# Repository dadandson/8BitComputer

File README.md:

# 8BitComputer
Hold eagle design for pcbs based on Ben Eaters 8 bit computer via bread boards

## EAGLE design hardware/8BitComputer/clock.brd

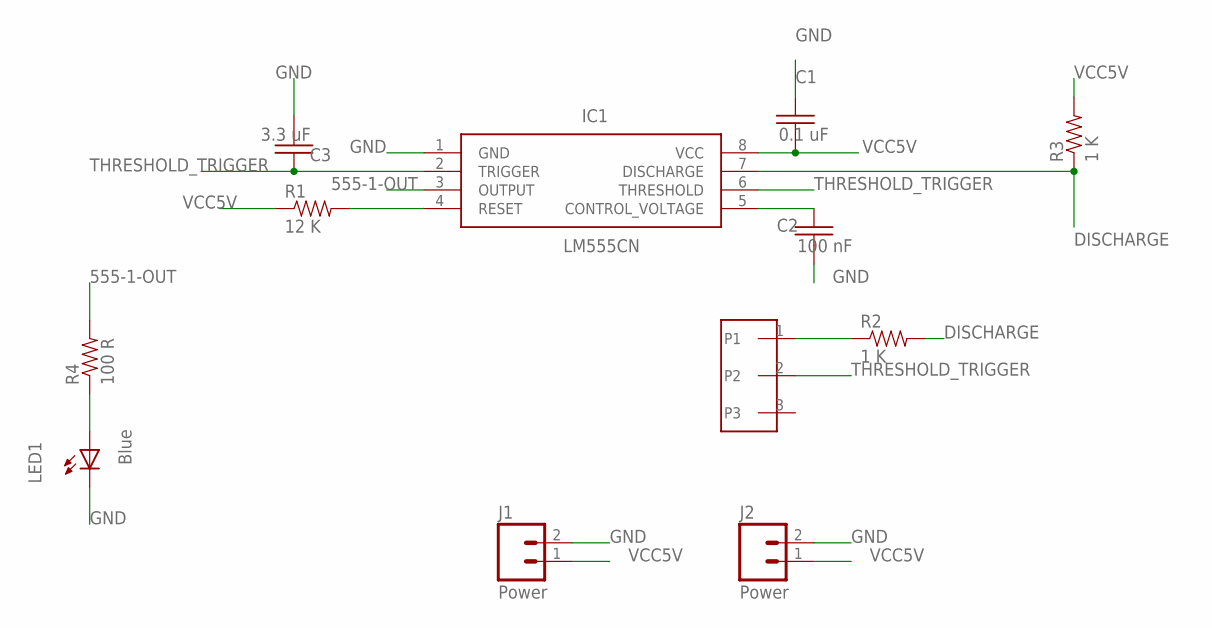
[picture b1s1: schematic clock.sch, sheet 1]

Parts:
C1: 0.1 uF; C0805
C2: 100 nF; C0805K
C3: 3.3 uF; C0805
IC1: LM555CN; DIP762W53P254L980H533Q8N
J1, J2: Power; 1X02
LED1: Blue; LED3MM-NS
R1: 12 K; 0805
R2, R3: 1 K; 0805
R4: 100 R; 0805
U$1: SQUARE-TRIMPOT-POTENTIOMETER; 3/8-SQUARE-TRIMPOT

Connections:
555-1-OUT: IC1.3 (OUTPUT), R4.2; also elsewhere on the board
DISCHARGE: IC1.7 (DISCHARGE), R2.2, R3.1
GND: C1.1, C2.2, C3.2, IC1.1 (GND), J1.2, J2.2, LED1.K (C); also elsewhere on the board
unnamed: IC1.4 (RESET), R1.2
unnamed: C2.1, IC1.5 (CONTROL_VOLTAGE)
unnamed: R2.1, U$1.1
unnamed: LED1.A, R4.1
THRESHOLD_TRIGGER: C3.1, IC1.2 (TRIGGER), IC1.6 (THRESHOLD), U$1.2
VCC5V: C1.2, IC1.8 (VCC), J1.1, J2.1, R1.1, R3.2; also elsewhere on the board

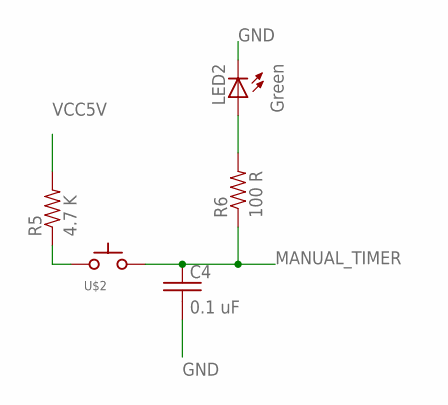
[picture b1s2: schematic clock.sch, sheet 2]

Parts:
C4: 0.1 uF; C0805
LED2: Green; LED3MM-NS
R5: 4.7 K; 0805
R6: 100 R; 0805
U$2: SWITCH_TACTILETACTILE_PIN; TACTILE-PTH

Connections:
GND: C4.2, LED2.K (C); also elsewhere on the board
MANUAL_TIMER: C4.1, R6.1, U$2.1 (A), U$2.2 (A); also elsewhere on the board
unnamed: LED2.A, R6.2
unnamed: R5.1, U$2.3 (C), U$2.4 (C)
VCC5V: R5.2; also elsewhere on the board

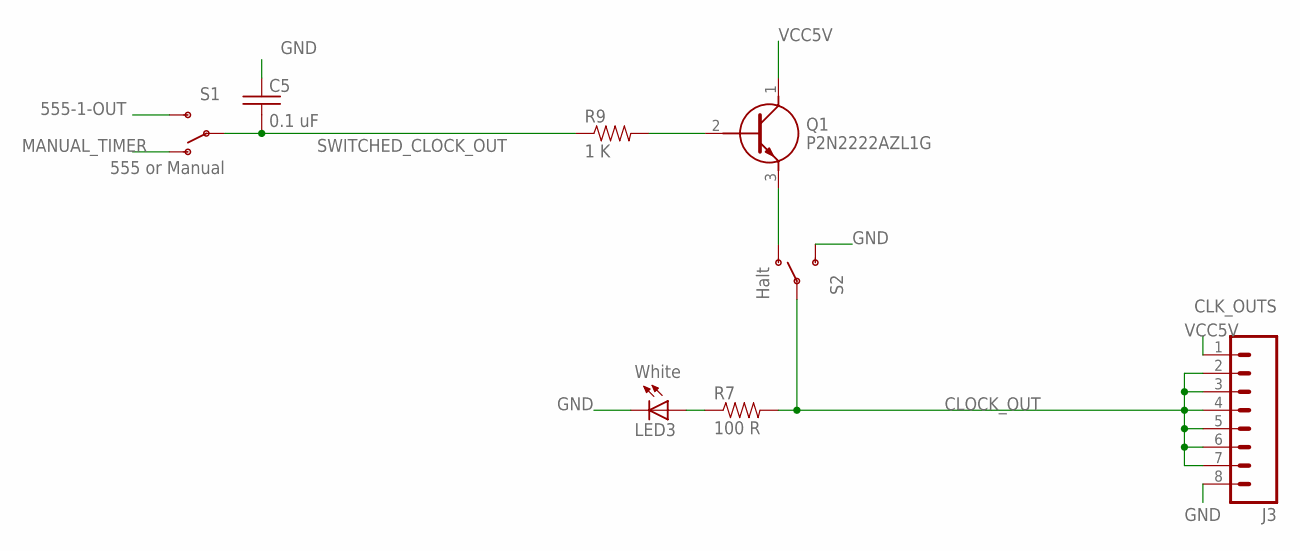
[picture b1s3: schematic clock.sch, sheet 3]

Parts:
C5: 0.1 uF; C0805
J3: CLK_OUTS; 1X08
LED3: White; LED3MM-NS
Q1: P2N2222AZL1G; 2N6027
R7: 100 R; 0805
R9: 1 K; 0805
S1: 555 or Manual; SWITCH-SPDT_KIT
S2: Halt; SWITCH-SPDT_KIT

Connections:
555-1-OUT: S1.3 (S); also elsewhere on the board
CLOCK_OUT: J3.2, J3.3, J3.4, J3.5, J3.6, J3.7, R7.2, S2.2
GND: C5.1, J3.8, LED3.K (C), S2.3 (S); also elsewhere on the board
MANUAL_TIMER: S1.1 (O); also elsewhere on the board
unnamed: LED3.A, R7.1
unnamed: Q1.3 (E), S2.1 (O)
unnamed: Q1.2 (B), R9.2
SWITCHED_CLOCK_OUT: C5.2, R9.1, S1.2
VCC5V: J3.1, Q1.1 (C); also elsewhere on the board

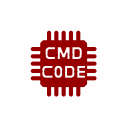
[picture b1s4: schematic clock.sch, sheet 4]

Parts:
U$3: CMD_C0DE_LOGOCMD_CODE_LOGO_TOP_COPPER; CMD_C0DE_LOGO_TOP_COPPER

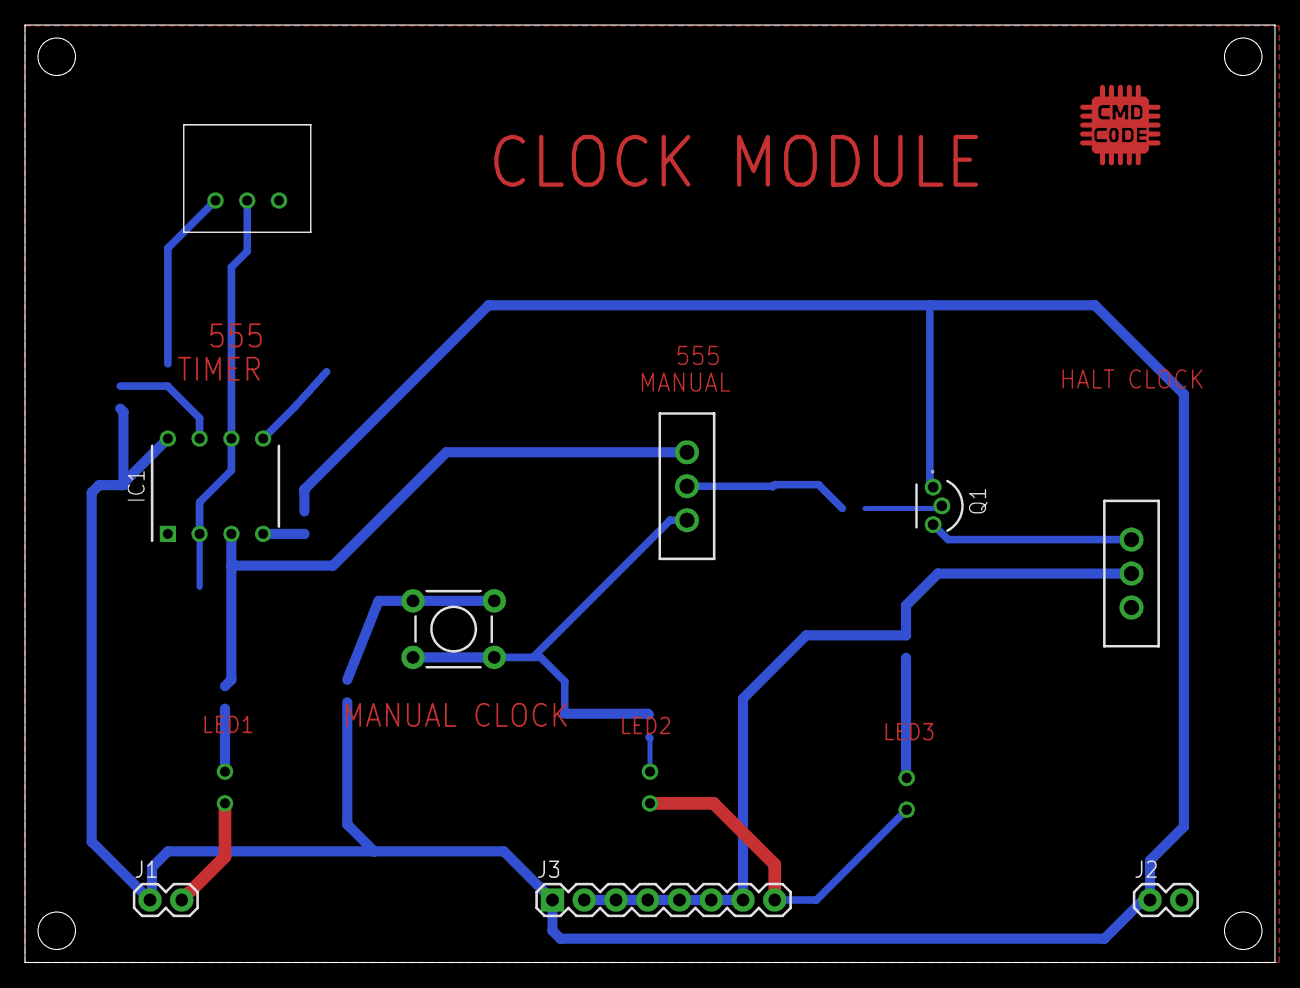
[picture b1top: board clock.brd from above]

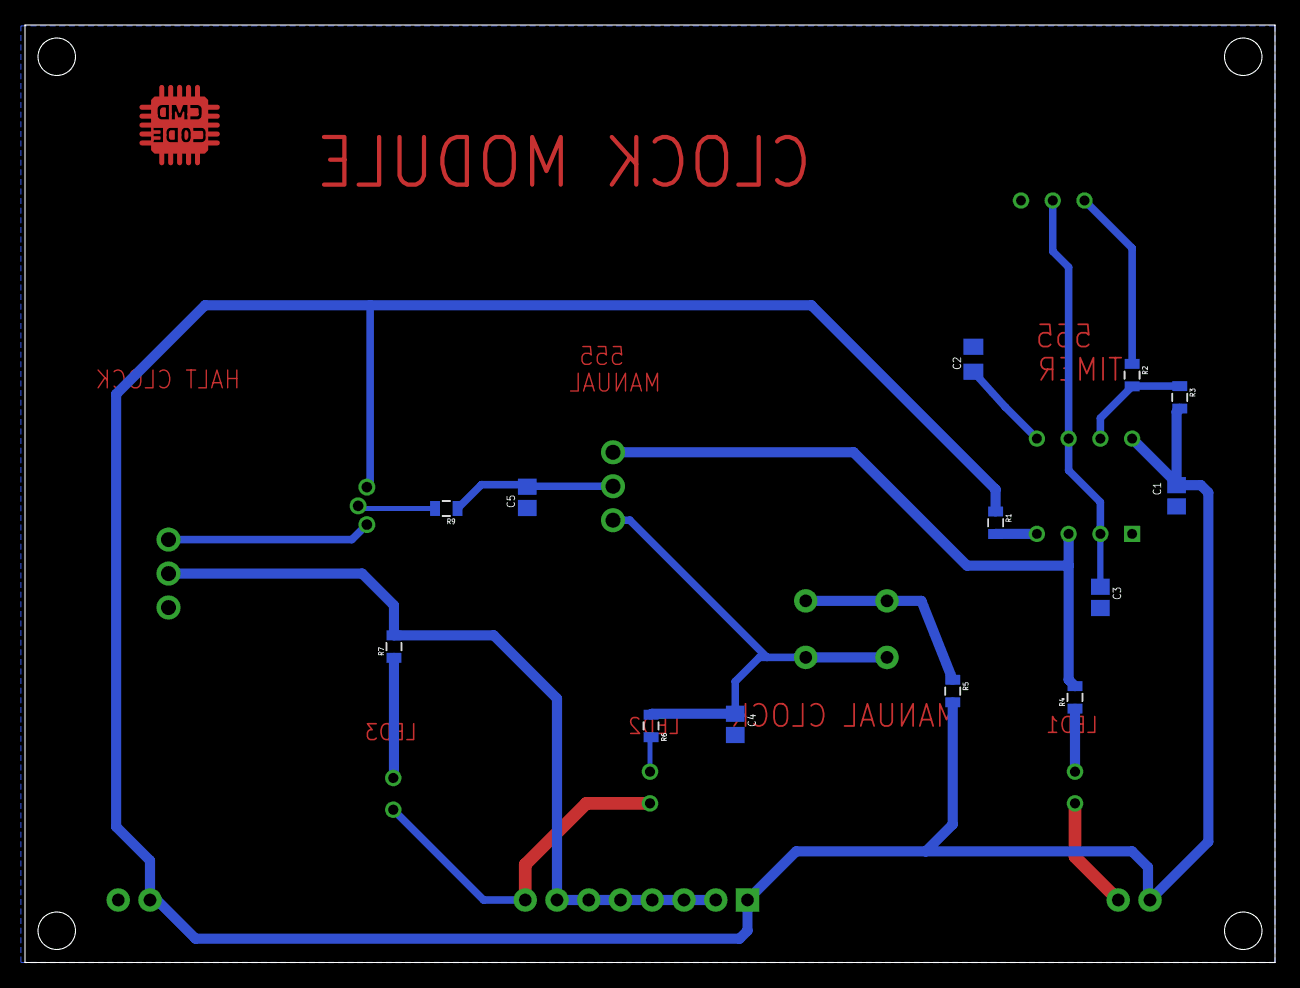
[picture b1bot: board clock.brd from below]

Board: 2 copper layers, 100.0 x 75.0 mm, 26 parts (13 on the bottom side), 17 nets.

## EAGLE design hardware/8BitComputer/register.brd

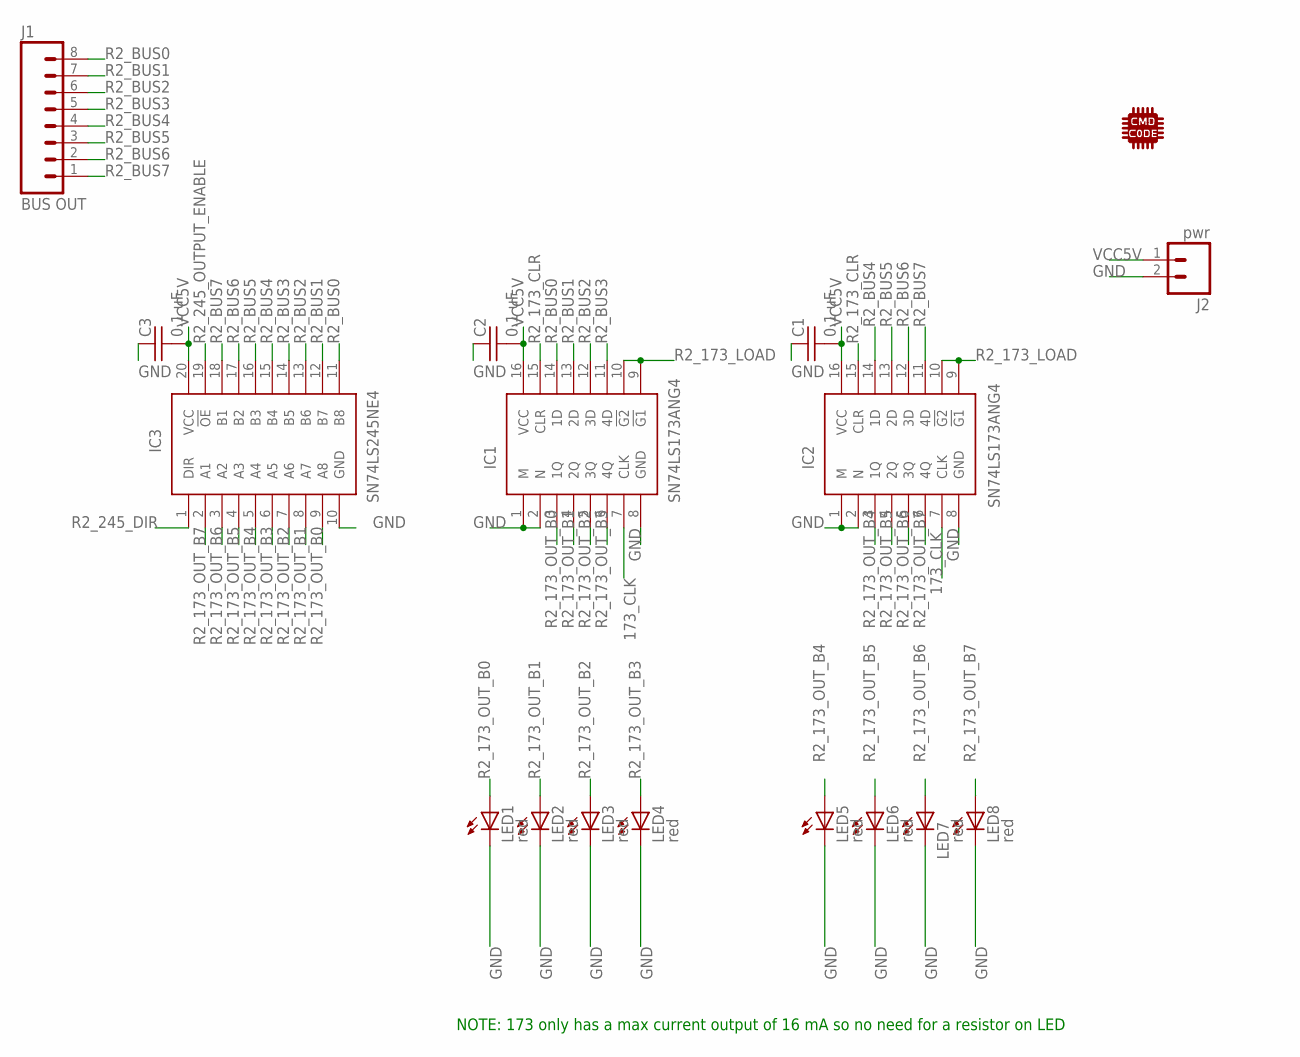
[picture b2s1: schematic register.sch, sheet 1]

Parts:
C1, C2, C3: 0.1 uF; C075-032X103
IC1, IC2: SN74LS173ANG4; DIP794W53P254L1930H508Q16N
IC3: SN74LS245NE4; DIP794W53P254L2540H508Q20N
J1: BUS OUT; 1X08_ROUND
J2: pwr; 1X02
LED1, LED2, LED3, LED4, LED5, LED6, LED7, LED8: red; LED3MM
U$1: CMD_C0DE_LOGOCMD_CODE_LOGO_TOP_COPPER; CMD_C0DE_LOGO_TOP_COPPER

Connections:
173_CLK: IC1.7 (CLK), IC2.7 (CLK); also elsewhere on the board
GND: C1.1, C2.1, C3.1, IC1.1 (M), IC1.2 (N), IC1.8 (GND), IC2.1 (M), IC2.2 (N), IC2.8 (GND), IC3.10 (GND), J2.2, LED1.K (C), LED2.K (C), LED3.K (C), LED4.K (C), LED5.K (C), LED6.K (C), LED7.K (C), LED8.K (C); also elsewhere on the board
R2_173_CLR: IC1.15 (CLR), IC2.15 (CLR); also elsewhere on the board
R2_173_LOAD: IC1.9 (!G1), IC1.10 (!G2), IC2.9 (!G1), IC2.10 (!G2); also elsewhere on the board
R2_173_OUT_B0: IC1.3 (1Q), IC3.9 (A8), LED1.A
R2_173_OUT_B1: IC1.4 (2Q), IC3.8 (A7), LED2.A
R2_173_OUT_B2: IC1.5 (3Q), IC3.7 (A6), LED3.A
R2_173_OUT_B3: IC1.6 (4Q), IC3.6 (A5), LED4.A
R2_173_OUT_B4: IC2.3 (1Q), IC3.5 (A4), LED5.A
R2_173_OUT_B5: IC2.4 (2Q), IC3.4 (A3), LED6.A
R2_173_OUT_B6: IC2.5 (3Q), IC3.3 (A2), LED7.A
R2_173_OUT_B7: IC2.6 (4Q), IC3.2 (A1), LED8.A
R2_245_DIR: IC3.1 (DIR); also elsewhere on the board
R2_245_OUTPUT_ENABLE: IC3.19 (!OE); also elsewhere on the board
R2_BUS0: IC1.14 (1D), IC3.11 (B8), J1.8
R2_BUS1: IC1.13 (2D), IC3.12 (B7), J1.7
R2_BUS2: IC1.12 (3D), IC3.13 (B6), J1.6
R2_BUS3: IC1.11 (4D), IC3.14 (B5), J1.5
R2_BUS4: IC2.14 (1D), IC3.15 (B4), J1.4
R2_BUS5: IC2.13 (2D), IC3.16 (B3), J1.3
R2_BUS6: IC2.12 (3D), IC3.17 (B2), J1.2
R2_BUS7: IC2.11 (4D), IC3.18 (B1), J1.1
VCC5V: C1.2, C2.2, C3.2, IC1.16 (VCC), IC2.16 (VCC), IC3.20 (VCC), J2.1; also elsewhere on the board

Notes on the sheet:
NOTE: 173 only has a max current output of 16 mA so no need for a resistor on LED

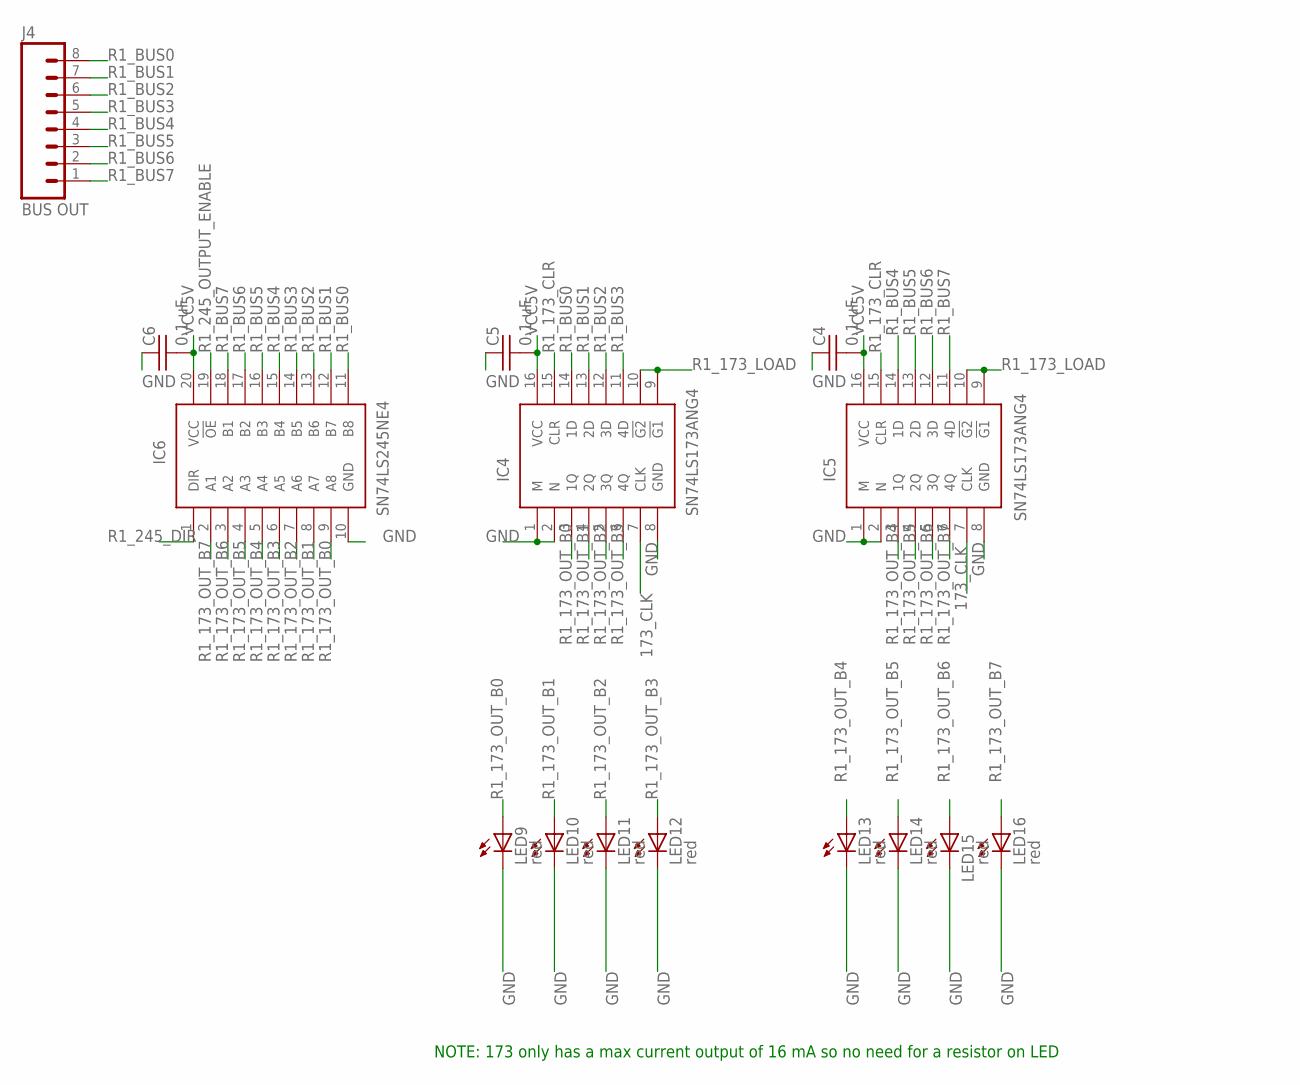
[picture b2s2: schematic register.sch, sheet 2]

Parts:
C4, C5, C6: 0.1 uF; C075-032X103
IC4, IC5: SN74LS173ANG4; DIP794W53P254L1930H508Q16N
IC6: SN74LS245NE4; DIP794W53P254L2540H508Q20N
J4: BUS OUT; 1X08_ROUND
LED9, LED10, LED11, LED12, LED13, LED14, LED15, LED16: red; LED3MM

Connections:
173_CLK: IC4.7 (CLK), IC5.7 (CLK); also elsewhere on the board
GND: C4.1, C5.1, C6.1, IC4.1 (M), IC4.2 (N), IC4.8 (GND), IC5.1 (M), IC5.2 (N), IC5.8 (GND), IC6.10 (GND), LED9.K (C), LED10.K (C), LED11.K (C), LED12.K (C), LED13.K (C), LED14.K (C), LED15.K (C), LED16.K (C); also elsewhere on the board
R1_173_CLR: IC4.15 (CLR), IC5.15 (CLR); also elsewhere on the board
R1_173_LOAD: IC4.9 (!G1), IC4.10 (!G2), IC5.9 (!G1), IC5.10 (!G2); also elsewhere on the board
R1_173_OUT_B0: IC4.3 (1Q), IC6.9 (A8), LED9.A
R1_173_OUT_B1: IC4.4 (2Q), IC6.8 (A7), LED10.A
R1_173_OUT_B2: IC4.5 (3Q), IC6.7 (A6), LED11.A
R1_173_OUT_B3: IC4.6 (4Q), IC6.6 (A5), LED12.A
R1_173_OUT_B4: IC5.3 (1Q), IC6.5 (A4), LED13.A
R1_173_OUT_B5: IC5.4 (2Q), IC6.4 (A3), LED14.A
R1_173_OUT_B6: IC5.5 (3Q), IC6.3 (A2), LED15.A
R1_173_OUT_B7: IC5.6 (4Q), IC6.2 (A1), LED16.A
R1_245_DIR: IC6.1 (DIR); also elsewhere on the board
R1_245_OUTPUT_ENABLE: IC6.19 (!OE); also elsewhere on the board
R1_BUS0: IC4.14 (1D), IC6.11 (B8), J4.8
R1_BUS1: IC4.13 (2D), IC6.12 (B7), J4.7
R1_BUS2: IC4.12 (3D), IC6.13 (B6), J4.6
R1_BUS3: IC4.11 (4D), IC6.14 (B5), J4.5
R1_BUS4: IC5.14 (1D), IC6.15 (B4), J4.4
R1_BUS5: IC5.13 (2D), IC6.16 (B3), J4.3
R1_BUS6: IC5.12 (3D), IC6.17 (B2), J4.2
R1_BUS7: IC5.11 (4D), IC6.18 (B1), J4.1
VCC5V: C4.2, C5.2, C6.2, IC4.16 (VCC), IC5.16 (VCC), IC6.20 (VCC); also elsewhere on the board

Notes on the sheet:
NOTE: 173 only has a max current output of 16 mA so no need for a resistor on LED

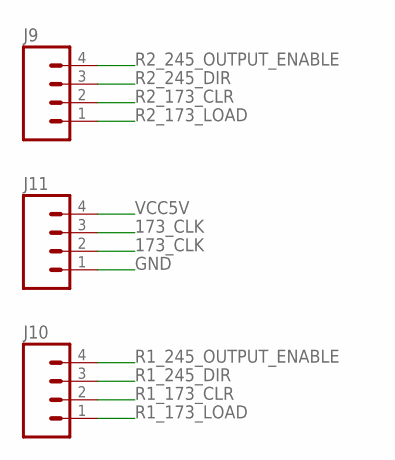
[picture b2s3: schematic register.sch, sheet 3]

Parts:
J9, J10, J11: M04PTH; 1X04

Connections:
173_CLK: J11.2, J11.3; also elsewhere on the board
GND: J11.1; also elsewhere on the board
R1_173_CLR: J10.2; also elsewhere on the board
R1_173_LOAD: J10.1; also elsewhere on the board
R1_245_DIR: J10.3; also elsewhere on the board
R1_245_OUTPUT_ENABLE: J10.4; also elsewhere on the board
R2_173_CLR: J9.2; also elsewhere on the board
R2_173_LOAD: J9.1; also elsewhere on the board
R2_245_DIR: J9.3; also elsewhere on the board
R2_245_OUTPUT_ENABLE: J9.4; also elsewhere on the board
VCC5V: J11.4; also elsewhere on the board

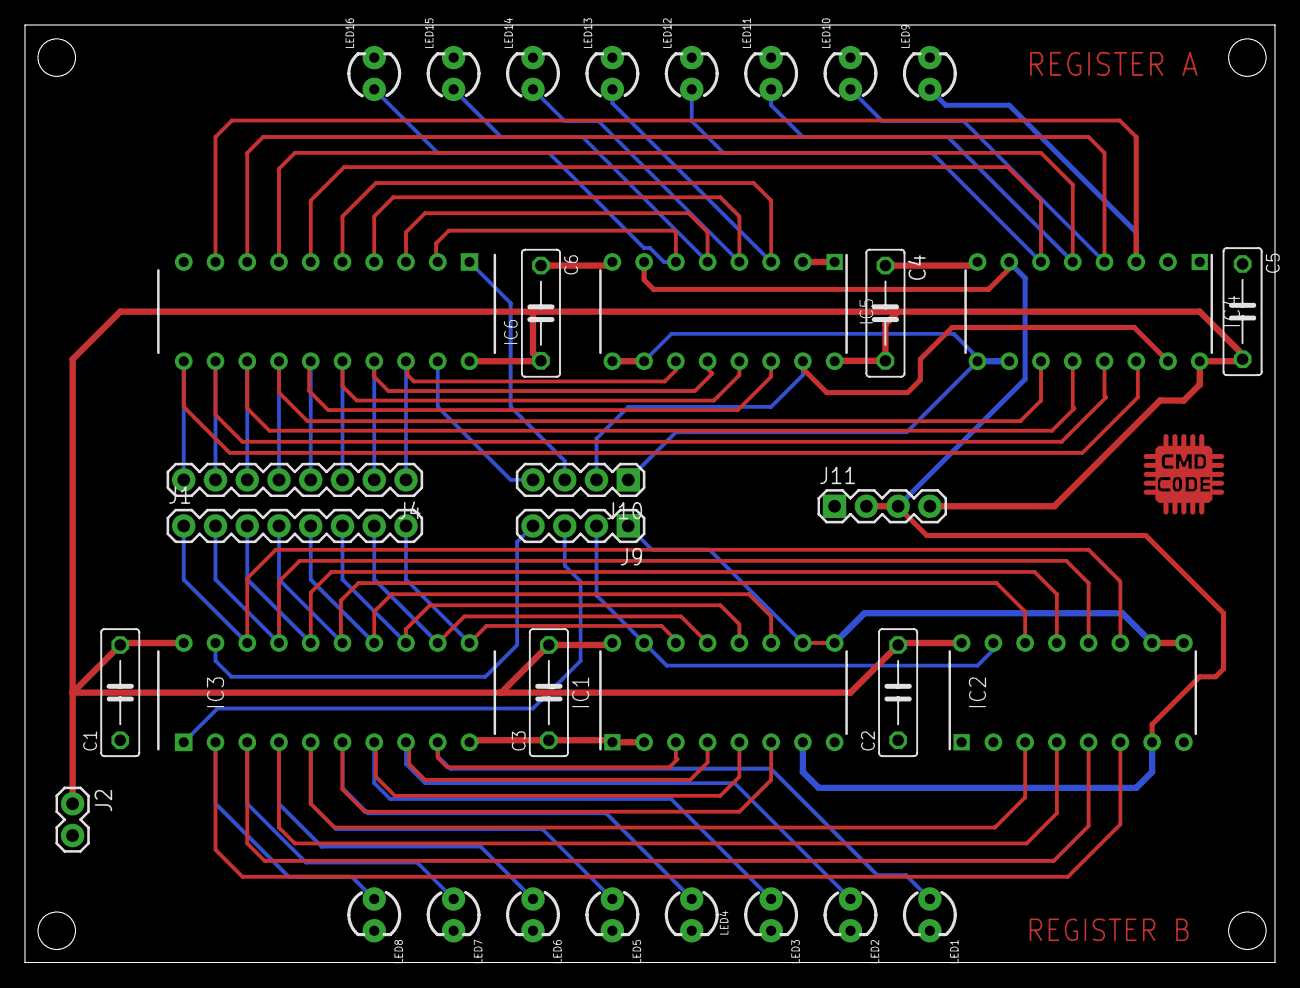
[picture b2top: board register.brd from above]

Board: 2 copper layers, 100.0 x 75.0 mm, 35 parts (0 on the bottom side), 43 nets.

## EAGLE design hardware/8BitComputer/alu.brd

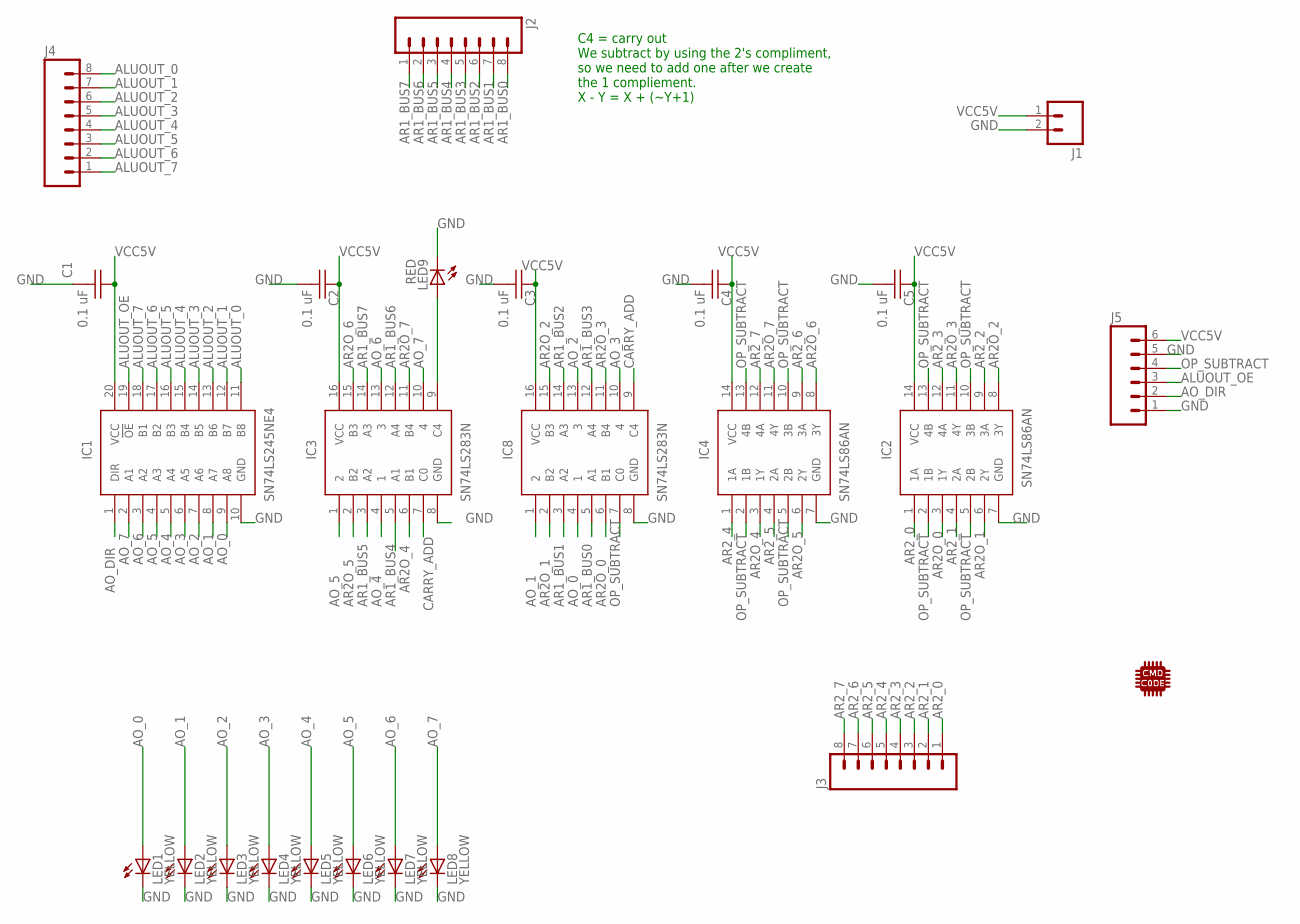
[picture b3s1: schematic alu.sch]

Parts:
C1, C2, C3, C4, C5: 0.1 uF; C050-025X075
IC1: SN74LS245NE4; DIP794W53P254L2540H508Q20N
IC2, IC4: SN74LS86AN; DIP254P762X508-14
IC3, IC8: SN74LS283N; DIP254P762X508-16
J1: M02PTH; 1X02
J2, J3, J4: M08SILK_FEMALE_PTH; 1X08
J5: M06SILK_FEMALE_PTH; 1X06
LED1, LED2, LED3, LED4, LED5, LED6, LED7, LED8: YELLOW; LED3MM-NS
LED9: RED; LED3MM-NS
U$1: CMD_C0DE_LOGOCMD_CODE_LOGO_TOP_COPPER; CMD_C0DE_LOGO_TOP_COPPER

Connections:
ALUOUT_0: IC1.11 (B8), J4.8
ALUOUT_1: IC1.12 (B7), J4.7
ALUOUT_2: IC1.13 (B6), J4.6
ALUOUT_3: IC1.14 (B5), J4.5
ALUOUT_4: IC1.15 (B4), J4.4
ALUOUT_5: IC1.16 (B3), J4.3
ALUOUT_6: IC1.17 (B2), J4.2
ALUOUT_7: IC1.18 (B1), J4.1
ALUOUT_OE: IC1.19 (!OE), J5.3
AO_0: IC1.9 (A8), IC8.4 (1), LED1.A
AO_1: IC1.8 (A7), IC8.1 (2), LED2.A
AO_2: IC1.7 (A6), IC8.13 (3), LED3.A
AO_3: IC1.6 (A5), IC8.10 (4), LED4.A
AO_4: IC1.5 (A4), IC3.4 (1), LED5.A
AO_5: IC1.4 (A3), IC3.1 (2), LED6.A
AO_6: IC1.3 (A2), IC3.13 (3), LED7.A
AO_7: IC1.2 (A1), IC3.10 (4), LED8.A
AO_DIR: IC1.1 (DIR), J5.2
AR1_BUS0: IC8.5 (A1), J2.8
AR1_BUS1: IC8.3 (A2), J2.7
AR1_BUS2: IC8.14 (A3), J2.6
AR1_BUS3: IC8.12 (A4), J2.5
AR1_BUS4: IC3.5 (A1), J2.4
AR1_BUS5: IC3.3 (A2), J2.3
AR1_BUS6: IC3.12 (A4), J2.2
AR1_BUS7: IC3.14 (A3), J2.1
AR2O_0: IC2.3 (1Y), IC8.6 (B1)
AR2O_1: IC2.6 (2Y), IC8.2 (B2)
AR2O_2: IC2.8 (3Y), IC8.15 (B3)
AR2O_3: IC2.11 (4Y), IC8.11 (B4)
AR2O_4: IC3.6 (B1), IC4.3 (1Y)
AR2O_5: IC3.2 (B2), IC4.6 (2Y)
AR2O_6: IC3.15 (B3), IC4.8 (3Y)
AR2O_7: IC3.11 (B4), IC4.11 (4Y)
AR2_0: IC2.1 (1A), J3.1
AR2_1: IC2.4 (2A), J3.2
AR2_2: IC2.9 (3A), J3.3
AR2_3: IC2.12 (4A), J3.4
AR2_4: IC4.1 (1A), J3.5
AR2_5: IC4.4 (2A), J3.6
AR2_6: IC4.9 (3A), J3.7
AR2_7: IC4.12 (4A), J3.8
CARRY_ADD: IC3.7 (C0), IC8.9 (C4)
GND: C1.2, C2.2, C3.2, C4.2, C5.2, IC1.10 (GND), IC2.7 (GND), IC3.8 (GND), IC4.7 (GND), IC8.8 (GND), J1.2, J5.1, J5.5, LED1.K (C), LED2.K (C), LED3.K (C), LED4.K (C), LED5.K (C), LED6.K (C), LED7.K (C), LED8.K (C), LED9.K (C)
unnamed: IC3.9 (C4), LED9.A
OP_SUBTRACT: IC2.2 (1B), IC2.5 (2B), IC2.10 (3B), IC2.13 (4B), IC4.2 (1B), IC4.5 (2B), IC4.10 (3B), IC4.13 (4B), IC8.7 (C0), J5.4
VCC5V: C1.1, C2.1, C3.1, C4.1, C5.1, IC1.20 (VCC), IC2.14 (VCC), IC3.16 (VCC), IC4.14 (VCC), IC8.16 (VCC), J1.1, J5.6

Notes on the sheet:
C4 = carry out We subtract by using the 2's compliment, so we need to add one after we create the 1 compliement. X - Y = X + (~Y+1)

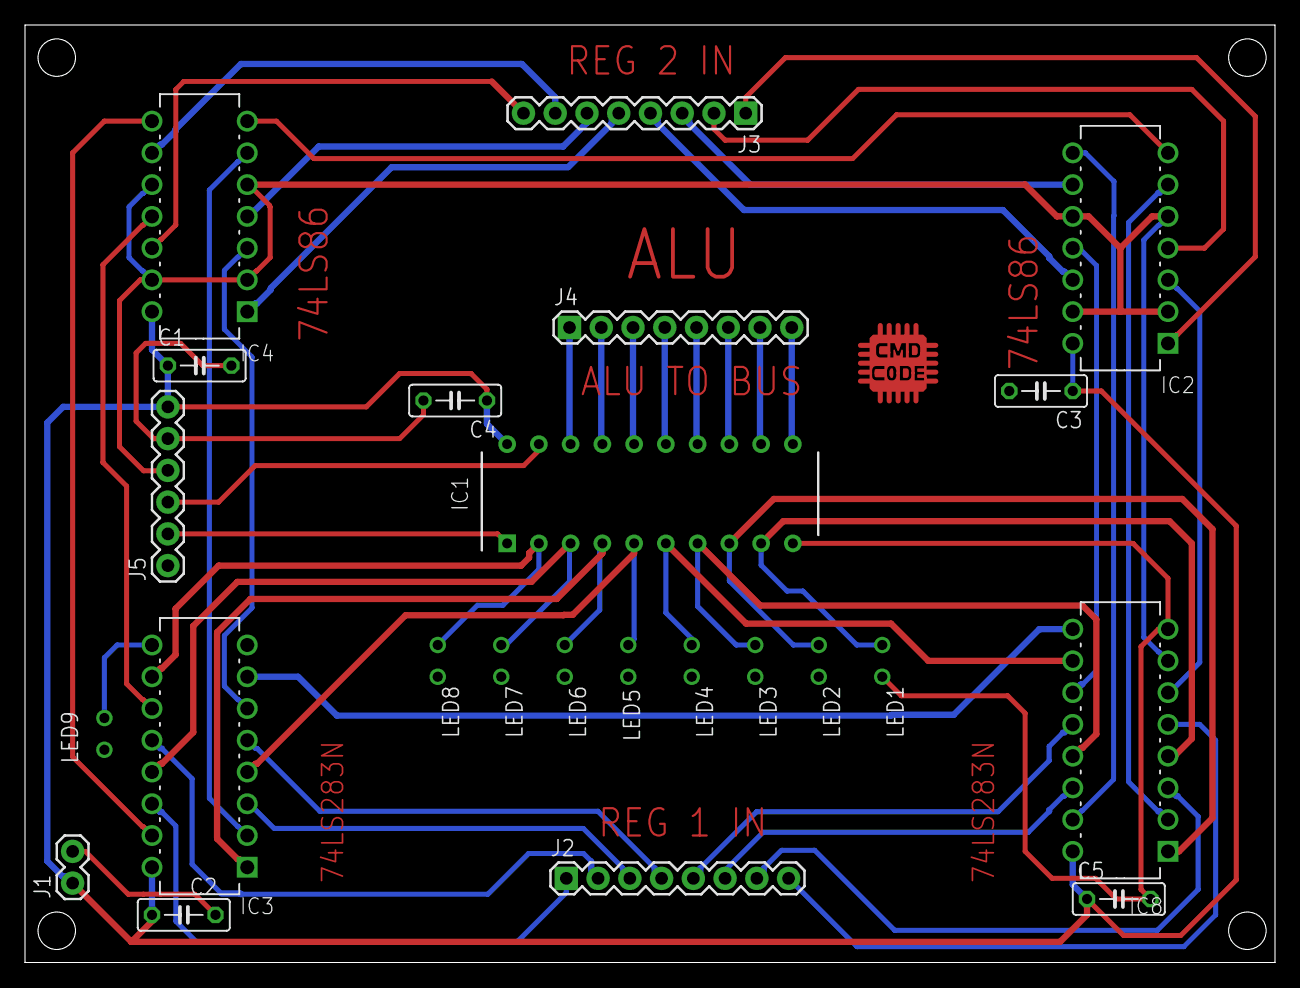
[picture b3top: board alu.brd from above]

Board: 2 copper layers, 100.0 x 75.0 mm, 25 parts (0 on the bottom side), 47 nets.

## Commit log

2019-04-15 first part of clock circuit complete schema, Board size determined
2019-04-15 just need to route
2019-04-15 organized board
2019-04-16 Sons first Routed Board
    Using ground plane on 2nd side of board to make layout easier.
2019-04-16 thicked traces: moved the resitor on halt switch so it can be pull up or pull down
2019-04-16 adding more docs
2019-04-21 lay out for size of our FR-4 boards
2019-04-22 started 8Bit REgister
2019-04-25 fixed missing trace on 555- miss spelled threshold :(
2019-04-27 3 registers and an instruction register complete
2019-04-27 added holes back
2019-04-28 updated clock to be a bit easier to solder by using bottom layer more. Thought here is that if the hole through pin only needs connection on one side then it should be the bottom so I don't have to s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
2019-04-28 added more text
2019-05-19 alu routed
2019-05-20 adding docs for ram
2019-11-03 prepring for SRAM module
2019-11-10 adding static ram chip updated all other boards to remove led resistors that aren't needed
2020-02-14 updated brd
2020-02-15 fixed clock module so it should actually work now
2020-02-16 adding gerbers and small change to brd
